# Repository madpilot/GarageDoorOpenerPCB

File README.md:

View this project on [CADLAB.io](https://cadlab.io/node/862). 

# GarageDoorOpenerPCB

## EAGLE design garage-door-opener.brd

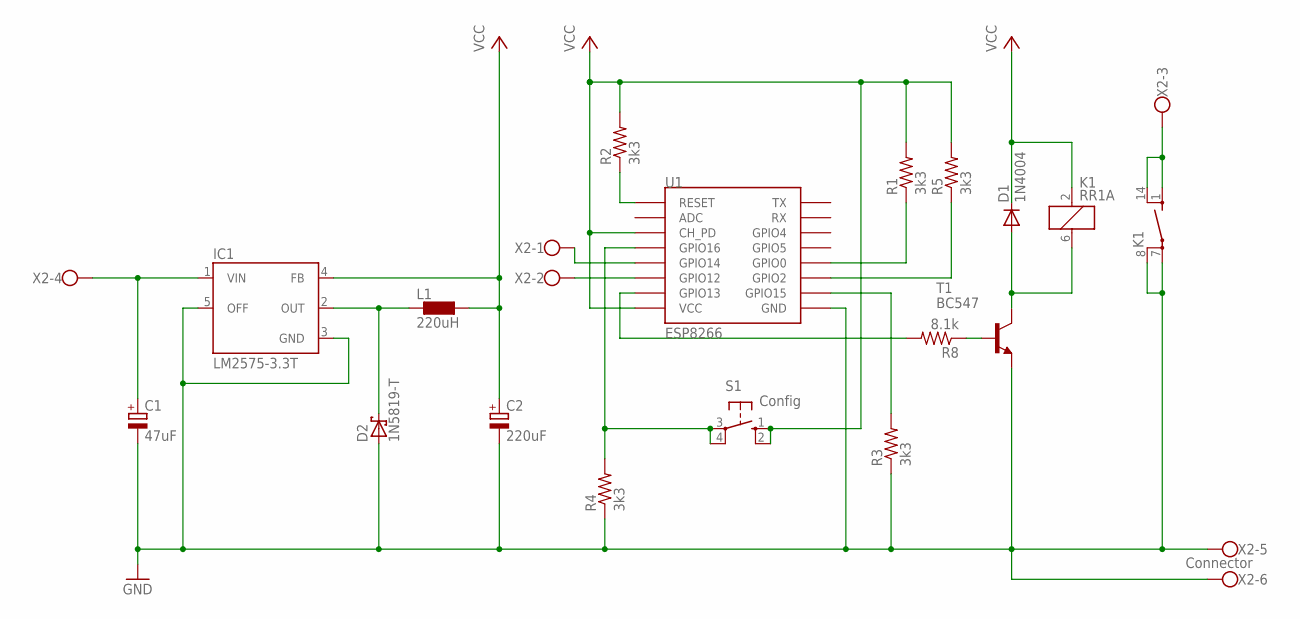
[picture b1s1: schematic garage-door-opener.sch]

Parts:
C1: 47uF; E5-4
C2: 220uF; E5-8,5
D1: 1N4004; DO41-10
D2: 1N5819-T; DO41-7.6
IC1: LM2575-3.3T; TO220-5
K1: RR1A
L1: 220uH; 0207/10
R1, R2, R3, R4, R5: 3k3; 0204/7
R8: 8.1k; 0204/7
S1: Config; B3F-10XX
T1: BC547; TO92
U1: ESP8266; ESP12-SMD-POGO
X2: Connector; W237-6

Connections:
GND: C1.-, C2.-, D2.A, IC1.3 (GND), IC1.5 (OFF), K1.7, K1.8, R3.1, R4.1, T1.1 (E), U1.GND, X2.5, X2.6
unnamed: D1.A, K1.6 (2), T1.3 (C)
unnamed: R8.1, T1.2 (B)
unnamed: D2.C, IC1.2 (OUT), L1.2
unnamed: K1.1 (S), K1.14 (S), X2.3
unnamed: R3.2, U1.GPIO15
unnamed: R1.1, U1.GPIO0
unnamed: R2.1, U1.RESET
unnamed: R8.2, U1.GPIO13
unnamed: U1.GPIO12, X2.2
unnamed: U1.GPIO14, X2.1
unnamed: R4.2, S1.3, S1.4 (P1), U1.GPIO16
unnamed: R5.1, U1.GPIO2
VCC: C2.+, D1.C, IC1.4 (FB), K1.2 (1), L1.1, R1.2, R2.2, R5.2, S1.1 (S), S1.2 (S1), U1.CH_PD, U1.VCC
VIN: C1.+, IC1.1 (VIN), X2.4

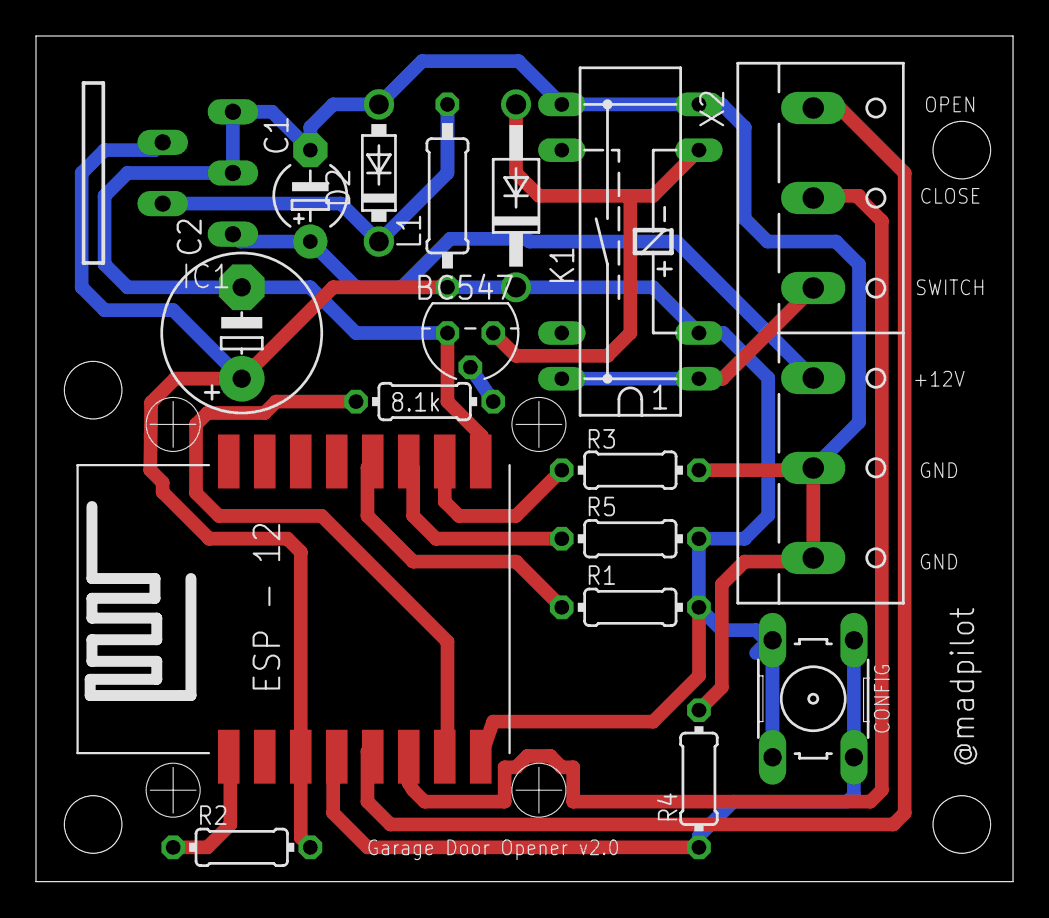
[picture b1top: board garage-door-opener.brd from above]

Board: 2 copper layers, 54.3 x 47.0 mm, 17 parts (0 on the bottom side), 15 nets.

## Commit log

2018-04-09 Initial check in
2018-04-09 Rerouting board to use switch mode PSU, and removing development switches and pads. Need to use the pogoable version of the ESP12
2018-04-10 Adding pull up resistors for all inputs for boot, hardwiring CH_PD, adding a config button to turn on the config website
2018-04-10 Fixing missing node on the VCC net, 12V in was incorrectly linked to VCC. Moved to VIN
2018-04-10 Adding pogo pins to ESP8266 for prgoramming. Fixing DRC errors - still some errors with the programmer mount screws.
2018-04-11 Using silk screen to indicate drill hold position for programmer (you probably don't want holes in a production board). For dev boards, you just need to manually drill 4 holes
2018-04-11 Backlink to CADLAB.io has been added.
2018-04-11 Lining up bottom screw holes
2018-04-11 Aligning resistors properly
2018-04-11 Cleaning out some routes. Eliminating a via
2018-04-11 Removing another via by rotating a resistor. They no longer ligne up, but one less via is a win, right?
2018-04-11 removed all the vias. Re-routed some tracks around the developer holes (sort of)
